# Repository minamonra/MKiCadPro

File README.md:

# MKiCadPro
MKiCadPro

Some of my projects

Use it - enjoy! :) ;)

minamonra@gmail.com

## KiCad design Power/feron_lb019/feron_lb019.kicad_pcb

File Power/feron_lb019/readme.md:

Блок питания 24 вольт, 150 Ватт, обратноход на ШИМ OB2269, частота при R18=27кОм - 65кГц.

Возможные варианты ШИМки CR6841/2, SG6841/2, SG5841/2, L2268/9, LD7551 (без Rt).

Размер корпуса 200x55.

[Обсудить можно тут.](https://anklab.ru/forum/index.php?topic=241.0)

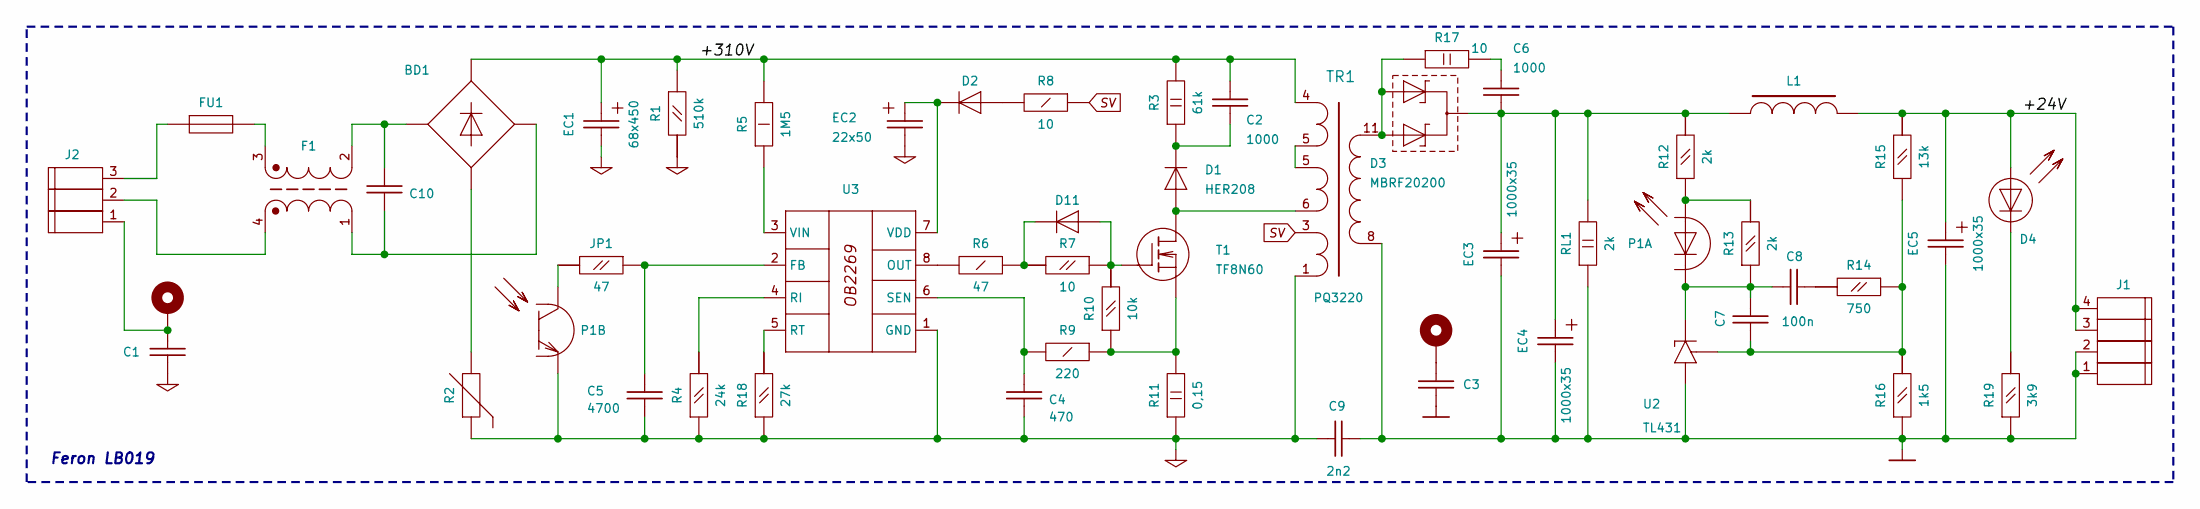
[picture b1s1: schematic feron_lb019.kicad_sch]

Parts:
BD1: BRIDGE; Diode_Bridge_19.0x3.5x10.0mm_P5.0mm
C1, C3: 1n; C_Disc_D5.0mm_W2.5mm_P5.00mm
C2, C6: 1000; C_Disc_D5.0mm_W2.5mm_P5.00mm
C4: 470; C_Disc_D5.0mm_W2.5mm_P5.00mm
C5: 4700; C_Disc_D5.0mm_W2.5mm_P5.00mm
C7: NA; C_Disc_D5.0mm_W2.5mm_P5.00mm
C8: 100n; C_Disc_D5.0mm_W2.5mm_P5.00mm
C9: 2n2; C_Disc_D5.0mm_W2.5mm_P5.00mm
C10: C_Rect_L9.0mm_W4.9mm_P7.50mm_MKT
D1: HER208; D_DO-15_P5.08mm_Vertical_KathodeUp
D2: DIODE; D_A-405_P10.16mm_Horizontal
D3: MBRF20200; TO-220-3-01
D4: LED; LED_D3.0mm
D11: DIODE; D_DO-34_SOD68_P10.16mm_Horizontal
EC1: 68x450; CP_L38.0mm_D18.0mm_P44.00mm_Horizontal
EC2: 22x50; CP_Radial_D6.3mm_P2.50mm
EC3, EC4, EC5: 1000x35; CP_Radial_D10.0mm_P5.00mm
F1: F; Filter-EMI-20x16_00
FU1: 1A; Fuse_Littelfuse_395Series
H2, H3: MountingHole_Pad; MountingHole_3.2mm_M3_DIN965_Pad
J1: Conn_4pin01; HB-8.25-4p
J2: Conn_3pin01; HB-8.25-3p
JP1: 47; R_Axial_DIN0207_L6.3mm_D2.5mm_P10.16mm_Horizontal
L1: LFERR; dross03
P1: PC817; DIP-4_W10.16mm_LongPads
R1: 510k; R_Axial_DIN0207_L6.3mm_D2.5mm_P10.16mm_Horizontal
R2: t°; RV_Disc_D12mm_W3.9mm_P7.5mm
R3: 61k; R_Axial_DIN0614_L14.3mm_D5.7mm_P5.08mm_Vertical
R4: 24k; R_Axial_DIN0207_L6.3mm_D2.5mm_P10.16mm_Horizontal
R5: 1M5; R_Axial_DIN0309_L9.0mm_D3.2mm_P15.24mm_Horizontal
R6: 47; R_Axial_DIN0207_L6.3mm_D2.5mm_P10.16mm_Horizontal
R7, R8: 10; R_Axial_DIN0207_L6.3mm_D2.5mm_P10.16mm_Horizontal
R9: 220; R_Axial_DIN0207_L6.3mm_D2.5mm_P10.16mm_Horizontal
R10: 10k; R_Axial_DIN0207_L6.3mm_D2.5mm_P10.16mm_Horizontal
R11: 0,15; R_Axial_DIN0516_L15.5mm_D5.0mm_P20.32mm_Horizontal
R12, R13: 2k; R_Axial_DIN0207_L6.3mm_D2.5mm_P10.16mm_Horizontal
R14: 750; R_Axial_DIN0207_L6.3mm_D2.5mm_P10.16mm_Horizontal
R15: 13k; R_Axial_DIN0207_L6.3mm_D2.5mm_P10.16mm_Horizontal
R16: 1k5; R_Axial_DIN0207_L6.3mm_D2.5mm_P10.16mm_Horizontal
R17: 10; R_Axial_DIN0516_L15.5mm_D5.0mm_P20.32mm_Horizontal
R18: 27k; R_Axial_DIN0207_L6.3mm_D2.5mm_P10.16mm_Horizontal
R19: 3k9; R_Axial_DIN0207_L6.3mm_D2.5mm_P10.16mm_Horizontal
RL1: 2k; R_Axial_DIN0516_L15.5mm_D5.0mm_P20.32mm_Horizontal
T1: TF8N60; TO-220-3-01
TR1: PQ3220; Transformer_PQ3220
U2: TL431; TO-92_IWm
U3: OB2268; DIP-8_W7.62mm

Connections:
/+24V: D4.2 (A), EC5.1, J1.3, J1.4, L1.2, R15.2
/+310V: BD1.1 (+), C2.2, EC1.1, R1.1, R3.2, R5.2, TR1.4
GND: C3.1, C9.1, EC3.2, EC4.2, EC5.2, J1.1, J1.2, R16.1, R19.1, RL1.1, TR1.7, TR1.8, TR1.9, U2.2 (A)
GND1: C1.1, C4.1, C5.1, C9.2, EC1.2, EC2.2, P1.3 (E), R1.2, R2.1, R4.1, R11.1, R18.1, TR1.1, U3.1 (GND)
unnamed: BD1.4 (-), R2.2
unnamed: BD1.2, C10.2, F1.2
unnamed: BD1.3, C10.1, F1.1
unnamed: C1.2, H2.1, J2.1
unnamed: C3.2, H3.1
unnamed: C6.2, R17.2
unnamed: C8.1, R14.2
unnamed: D1.2 (A), T1.2 (D), TR1.6
unnamed: C2.1, D1.1 (C), R3.1
unnamed: D2.2 (A), R8.2
unnamed: D2.1 (C), EC2.1, U3.7 (VDD)
unnamed: D3.1 (A1), D3.3 (A2), R17.1, TR1.10, TR1.11, TR1.12
unnamed: C6.1, D3.2 (K), EC3.1, EC4.1, L1.1, R12.2, RL1.2
unnamed: D4.1 (C), R19.2
unnamed: D11.2 (A), R7.1, R10.2, T1.1 (G)
unnamed: D11.1 (C), R6.1, R7.2
unnamed: F1.3, FU1.2
unnamed: F1.4, J2.2
unnamed: FU1.1, J2.3
unnamed: P1.1 (A), R12.1, R13.2
unnamed: C7.1, C8.2, P1.2 (C), R13.1, U2.3 (K)
unnamed: JP1.2, P1.4 (C)
unnamed: R9.1, R10.1, R11.2, T1.3 (S)
unnamed: C7.2, R14.1, R15.1, R16.2, U2.1 (REF)
unnamed: C5.2, JP1.1, U3.2 (FB)
unnamed: R6.2, U3.8 (OUT)
unnamed: R4.2, U3.4 (RI)
unnamed: R18.2, U3.5 (RT)
unnamed: C4.2, R9.2, U3.6 (SEN)
unnamed: R5.1, U3.3 (VIN)
SV: R8.1, TR1.3

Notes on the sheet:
Feron LB019

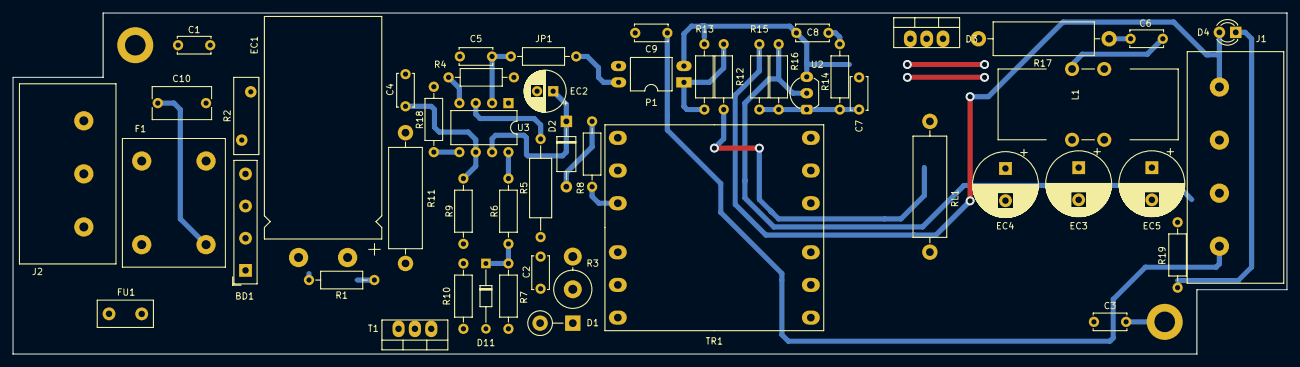
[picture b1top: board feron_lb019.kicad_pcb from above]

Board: 2 copper layers, 198.0 x 53.0 mm, 54 parts (0 on the bottom side), 35 nets.

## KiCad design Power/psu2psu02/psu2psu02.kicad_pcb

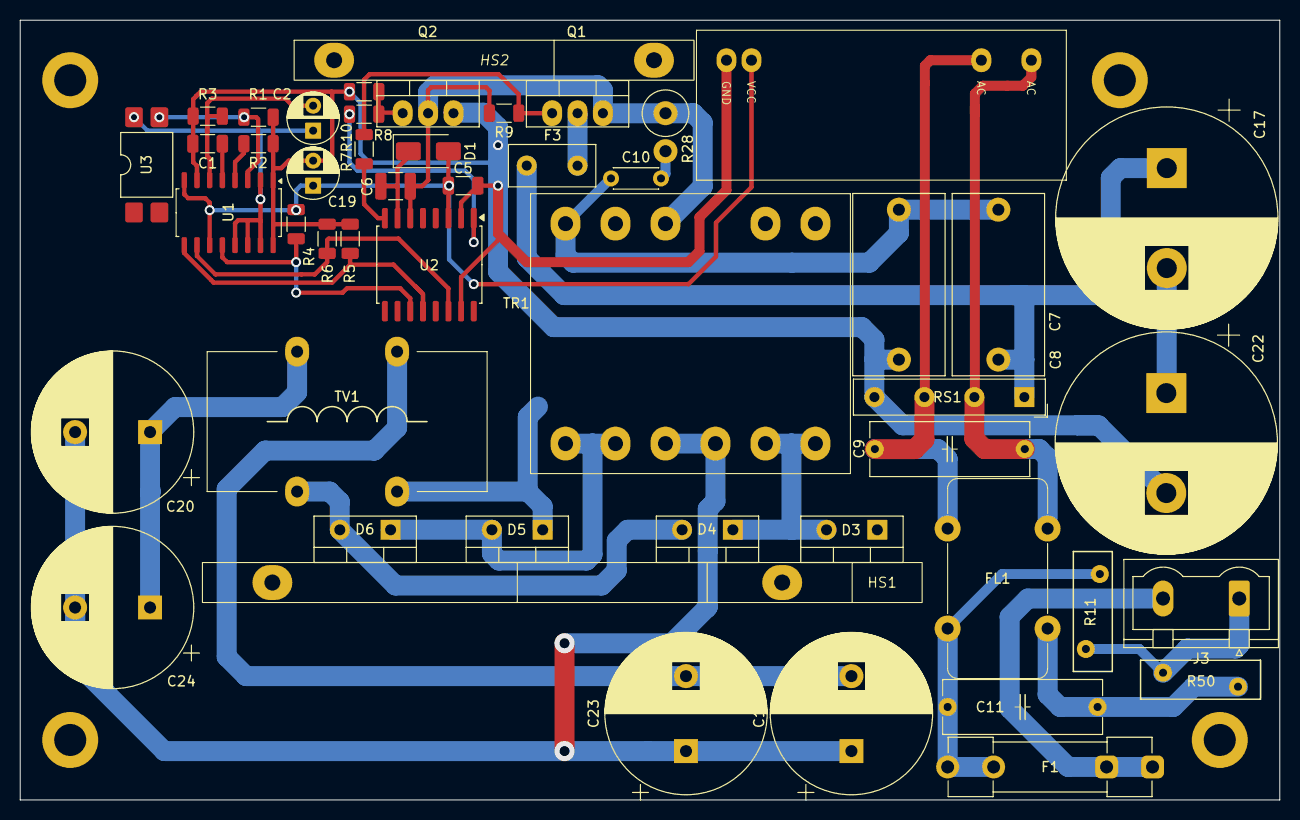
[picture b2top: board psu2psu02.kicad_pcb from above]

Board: 2 copper layers, 126.0 x 78.0 mm, 53 parts (0 on the bottom side), 34 nets.

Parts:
C1: 1000; C_1206_3216Metric
C2, C19: 10x35; CP_Radial_D5.0mm_P2.50mm
C5: 2,2; C_1206_3216Metric
C6: 2,2; C_1210_3225Metric
C7, C8: 1u; C_Rect_L18.0mm_W9.0mm_P15.00mm_FKS3_FKP3
C9, C11: 0,1; C_Rect_06-L16P15W5.8
C10: 4n7; C_Disc_D4.3mm_W1.9mm_P5.00mm
C17, C22: 330x200; CP_Radial_D22.0mm_P10.00mm_SnapIn
C18, C20, C23, C24: 1; CP_Radial_D16.0mm_P7.50mm
D1: ES1J; D_SMA
D3, D4, D5, D6: SF10A400H; TO-220-2_Vertical
F1: 1A; Fuseholder_Clip-5x20mm_Littelfuse_100_Inline_P20.50x4.60mm_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
F3: 3A; Fuse_Littelfuse_395Series
FL1: FEMI-FLEX01; EMIF02-FLEX
H1, H2, H3, H4: MountingHole; MountingHole_3.2mm_M3_DIN965_Pad
HS1: Heatsink_Pad; HeatsinkFLEX-200A-1
HS2: Heatsink_Pad; HeatsinkFLEX-200A-2
J3: Conn_2pin01; PhoenixContact_GMSTBVA_2,5_2-G-7,62_1x02_P7.62mm_Vertical
J6: ACDC_China-01; ACDC_China-04
Q1, Q2: 740; TO-220-3-01
R1, R9, R10: 1k; R_1206_3216Metric
R2, R5, R6: 10k; R_1206_3216Metric
R3: 11k; R_1206_3216Metric
R4: 27; R_1206_3216Metric
R7, R8: 33; R_1206_3216Metric
R11: 07K180; RV_Disc_D12mm_W3.9mm_P7.5mm
R28: 3k; RES2WV01
R50: t°; RV_Disc_D12mm_W3.9mm_P7.5mm
RS1: BRIDGE; Diode_Bridge_19.0x3.5x10.0mm_P5.0mm
TR1: HB-FLEX-200A-1; E36-FLEX-200A-P
TV1: TV; DRO05-FLEX-200A
U1: TL494IDR; SOIC-16_4.55x10.3mm_P1.27mm
U2: IR2113S; SOIC-16W_7.5x10.3mm_P1.27mm
U3: PC817; SMDIP-4_W9.53mm

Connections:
+HV: C7.2, C17.1, F3.2, RS1.1 (+)
/HV4: C6.1, Q1.3 (S), Q2.2 (D), R9.2, R28.1, TR1.4, U2.6 (Vs)
/HV6: C7.1, C8.2, C10.1, TR1.6
GND: C18.1, C20.2, C23.1, C24.2, TR1.9, TR1.10
GND2: C1.2, C5.1, C8.1, C19.2, C22.2, J6.4 (GND), Q2.3 (S), R1.1, R2.1, R3.1, R5.2, R6.2, R10.2, RS1.4 (-), U1.1 (1IN+), U1.7 (GND), U1.16 (2IN+), U2.2 (COM), U2.15 (Vss)
unnamed: C9.1, FL1.1, J6.2 (AC), RS1.3
unnamed: C9.2, FL1.2, J6.1 (AC), RS1.2
unnamed: C10.2, R28.2
unnamed: C11.1, F1.2, FL1.3, R11.1
unnamed: C11.2, FL1.4, R50.2
unnamed: C17.2, C22.1
unnamed: C18.2, C23.2, TV1.3
unnamed: C20.1, C24.1, TV1.4
unnamed: C6.2, D1.1 (C), U2.7 (Vb)
unnamed: D3.2 (A), D4.1 (C), TR1.11, TR1.12
unnamed: D3.1 (C), D5.1 (C), TV1.1
unnamed: D4.2 (A), D6.2 (A), TV1.2
unnamed: D5.2 (A), D6.1 (C), TR1.7, TR1.8
unnamed: F1.1, J3.2
unnamed: J3.1, R11.2, R50.1
unnamed: F3.1, Q1.2 (D)
unnamed: Q1.1 (G), R7.2, R9.1
unnamed: Q2.1 (G), R8.2, R10.1
unnamed: C2.1, U1.2 (1IN-), U1.13 (OTC), U1.14 (REF), U1.15 (2IN-), U3.4 (C)
unnamed: C1.1, U1.5 (CT)
unnamed: R2.2, U1.4 (DTC)
unnamed: R5.1, U1.9 (E1), U2.12 (Hin)
unnamed: R6.1, U1.10 (E2), U2.14 (Lin)
unnamed: R1.2, U1.3 (FB), U3.3 (E)
unnamed: C2.2, R3.2, U1.6 (RT)
unnamed: R4.1, U1.12 (VCC), U2.11 (Vdd)
unnamed: R7.1, U2.8 (HO)
unnamed: R8.1, U2.1 (LO)
VCC: C5.2, C19.1, D1.2 (A), J6.3 (VCC), R4.2, U1.8 (C1), U1.11 (C2), U2.3 (Vcc)

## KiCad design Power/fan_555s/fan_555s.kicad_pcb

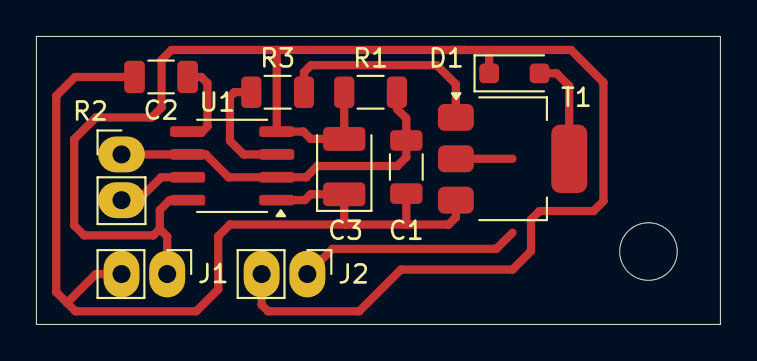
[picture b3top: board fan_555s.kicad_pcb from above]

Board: 2 copper layers, 38.0 x 16.0 mm, 12 parts (0 on the bottom side), 8 nets.

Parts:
C1, C2: 0,1; C_1206_3216Metric
C3: 10,0; CP_EIA-3528-21_Kemet-B
D1: 4148; D_SOD-123F
H1: MountingHole; MountingHole_3.2mm_M3
J1, J2: Conn_2pin01; PinHeader_1x02_P2.54mm_Vertical
R1: 22k; R_1206_3216Metric
R2: 10k/NTC; PinHeader_1x02_P2.54mm_Vertical
R3: 100; R_1206_3216Metric
T1: 1N60G; SOT-223-3_TabPin2
U1: NE555; SOIC-8_3.9x4.9mm_P1.27mm

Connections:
GND: C1.1, C2.1, C3.1, J1.2, T1.3 (S), U1.1 (GND)
unnamed: D1.2 (A), J2.1, T1.2 (D)
unnamed: C3.2, D1.1 (C), J1.1, J2.2, R1.2, U1.4 (RST), U1.8 (VCC)
unnamed: R3.2, T1.1 (G)
unnamed: C2.2, U1.5 (CTL)
unnamed: R2.2, U1.7 (DIS)
unnamed: R3.1, U1.3 (OUT)
unnamed: C1.2, R1.1, R2.1, U1.2 (TRG), U1.6 (THR)

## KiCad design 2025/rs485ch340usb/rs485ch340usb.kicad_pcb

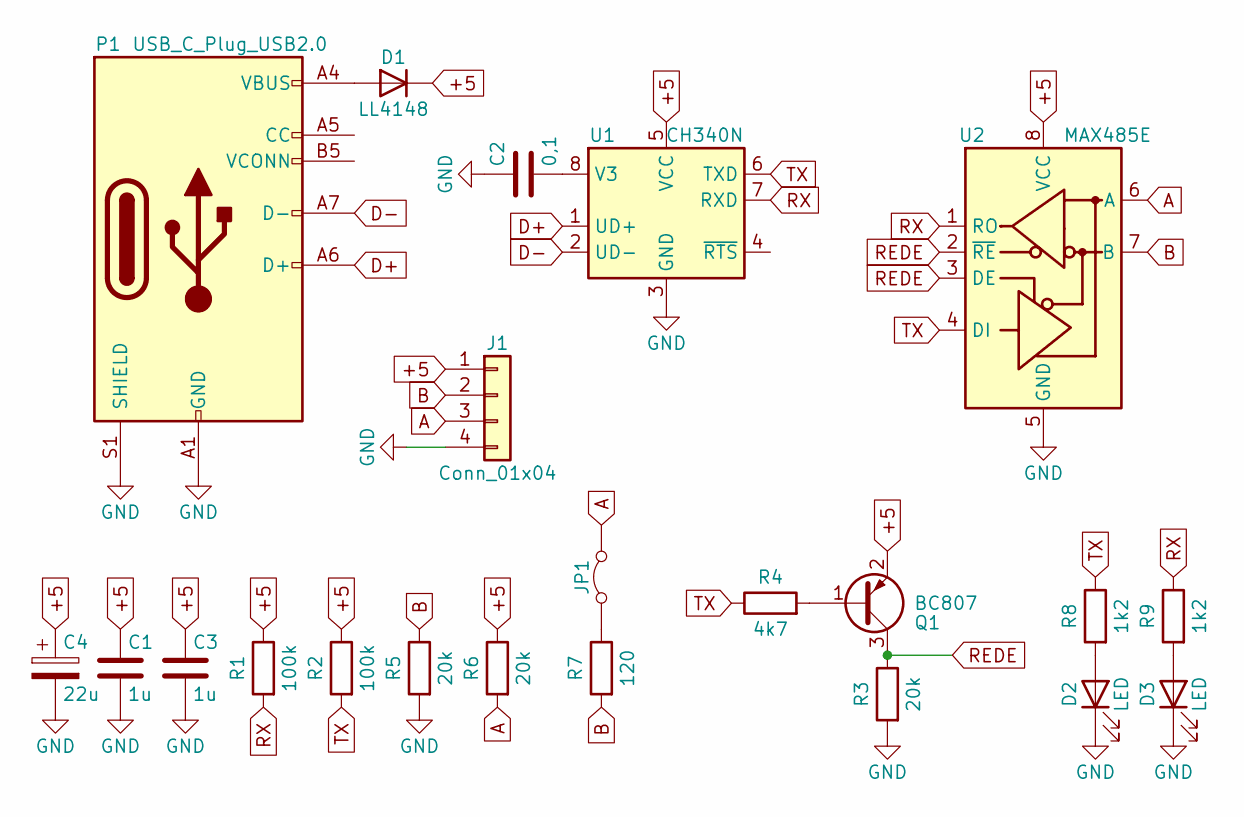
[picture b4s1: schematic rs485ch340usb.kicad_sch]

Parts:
C1, C3: 1u; C_1206_3216Metric
C2: 0,1; C_1206_3216Metric
C4: 22u; CP_EIA-3528-21_Kemet-B
D1: LL4148; D_MiniMELF
D2, D3: LED; LED_1206_3216Metric
J1: Conn_01x04; TerminalBlock_bornier-4_P5.08mm
JP1: Jumper_2_Bridged; PinHeader_1x02_P2.54mm_Vertical
P1: USB_C_Plug_USB2.0; USB_C_Plug_JAE_DX07P024AJ1
Q1: BC807; SOT-23
R1, R2: 100k; R_1206_3216Metric
R3, R5, R6: 20k; R_1206_3216Metric
R4: 4k7; R_1206_3216Metric
R7: 120; R_1206_3216Metric
R8, R9: 1k2; R_1206_3216Metric
U1: CH340N; SOP-8_3.9x4.9mm_P1.27mm
U2: MAX485E; SOIC-8_3.9x4.9mm_P1.27mm

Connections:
+5: C1.1, C3.1, C4.1, D1.1 (K), J1.1, Q1.2 (E), R1.1, R2.1, R6.1, U1.5 (VCC), U2.8 (VCC)
A: J1.3, JP1.2 (B), R6.2, U2.6 (A)
B: J1.2, R5.1, R7.2, U2.7 (B)
D+: P1.A6 (D+), U1.1 (UD+)
D-: P1.A7 (D-), U1.2 (UD-)
GND: C1.2, C2.1, C3.2, C4.2, D2.1 (K), D3.1 (K), J1.4, P1.A1 (GND), P1.A12 (GND), P1.B1 (GND), P1.B12 (GND), P1.S1 (SHIELD), R3.2, R5.2, U1.3 (GND), U2.5 (GND)
unnamed: D1.2 (A), P1.A4 (VBUS), P1.A9 (VBUS), P1.B4 (VBUS), P1.B9 (VBUS)
unnamed: D2.2 (A), R8.2
unnamed: D3.2 (A), R9.2
unnamed: JP1.1 (A), R7.1
unnamed: Q1.1 (B), R4.2
unnamed: C2.2, U1.8 (V3)
REDE: Q1.3 (C), R3.1, U2.2 (~RE), U2.3 (DE)
RX: R1.2, R9.1, U1.7 (RXD), U2.1 (RO)
TX: R2.2, R4.1, R8.1, U1.6 (TXD), U2.4 (DI)

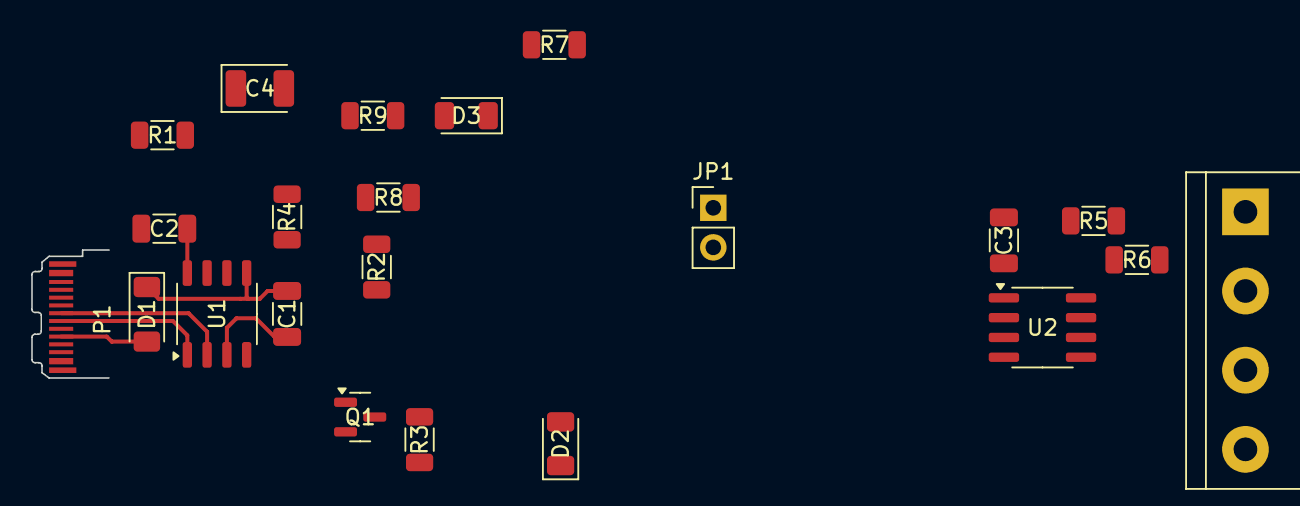
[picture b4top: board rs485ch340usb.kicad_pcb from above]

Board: 2 copper layers, 22 parts (0 on the bottom side), 15 nets.

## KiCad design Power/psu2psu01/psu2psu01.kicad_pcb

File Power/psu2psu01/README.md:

For details see:
https://anklab.ru/forum/index.php?topic=197

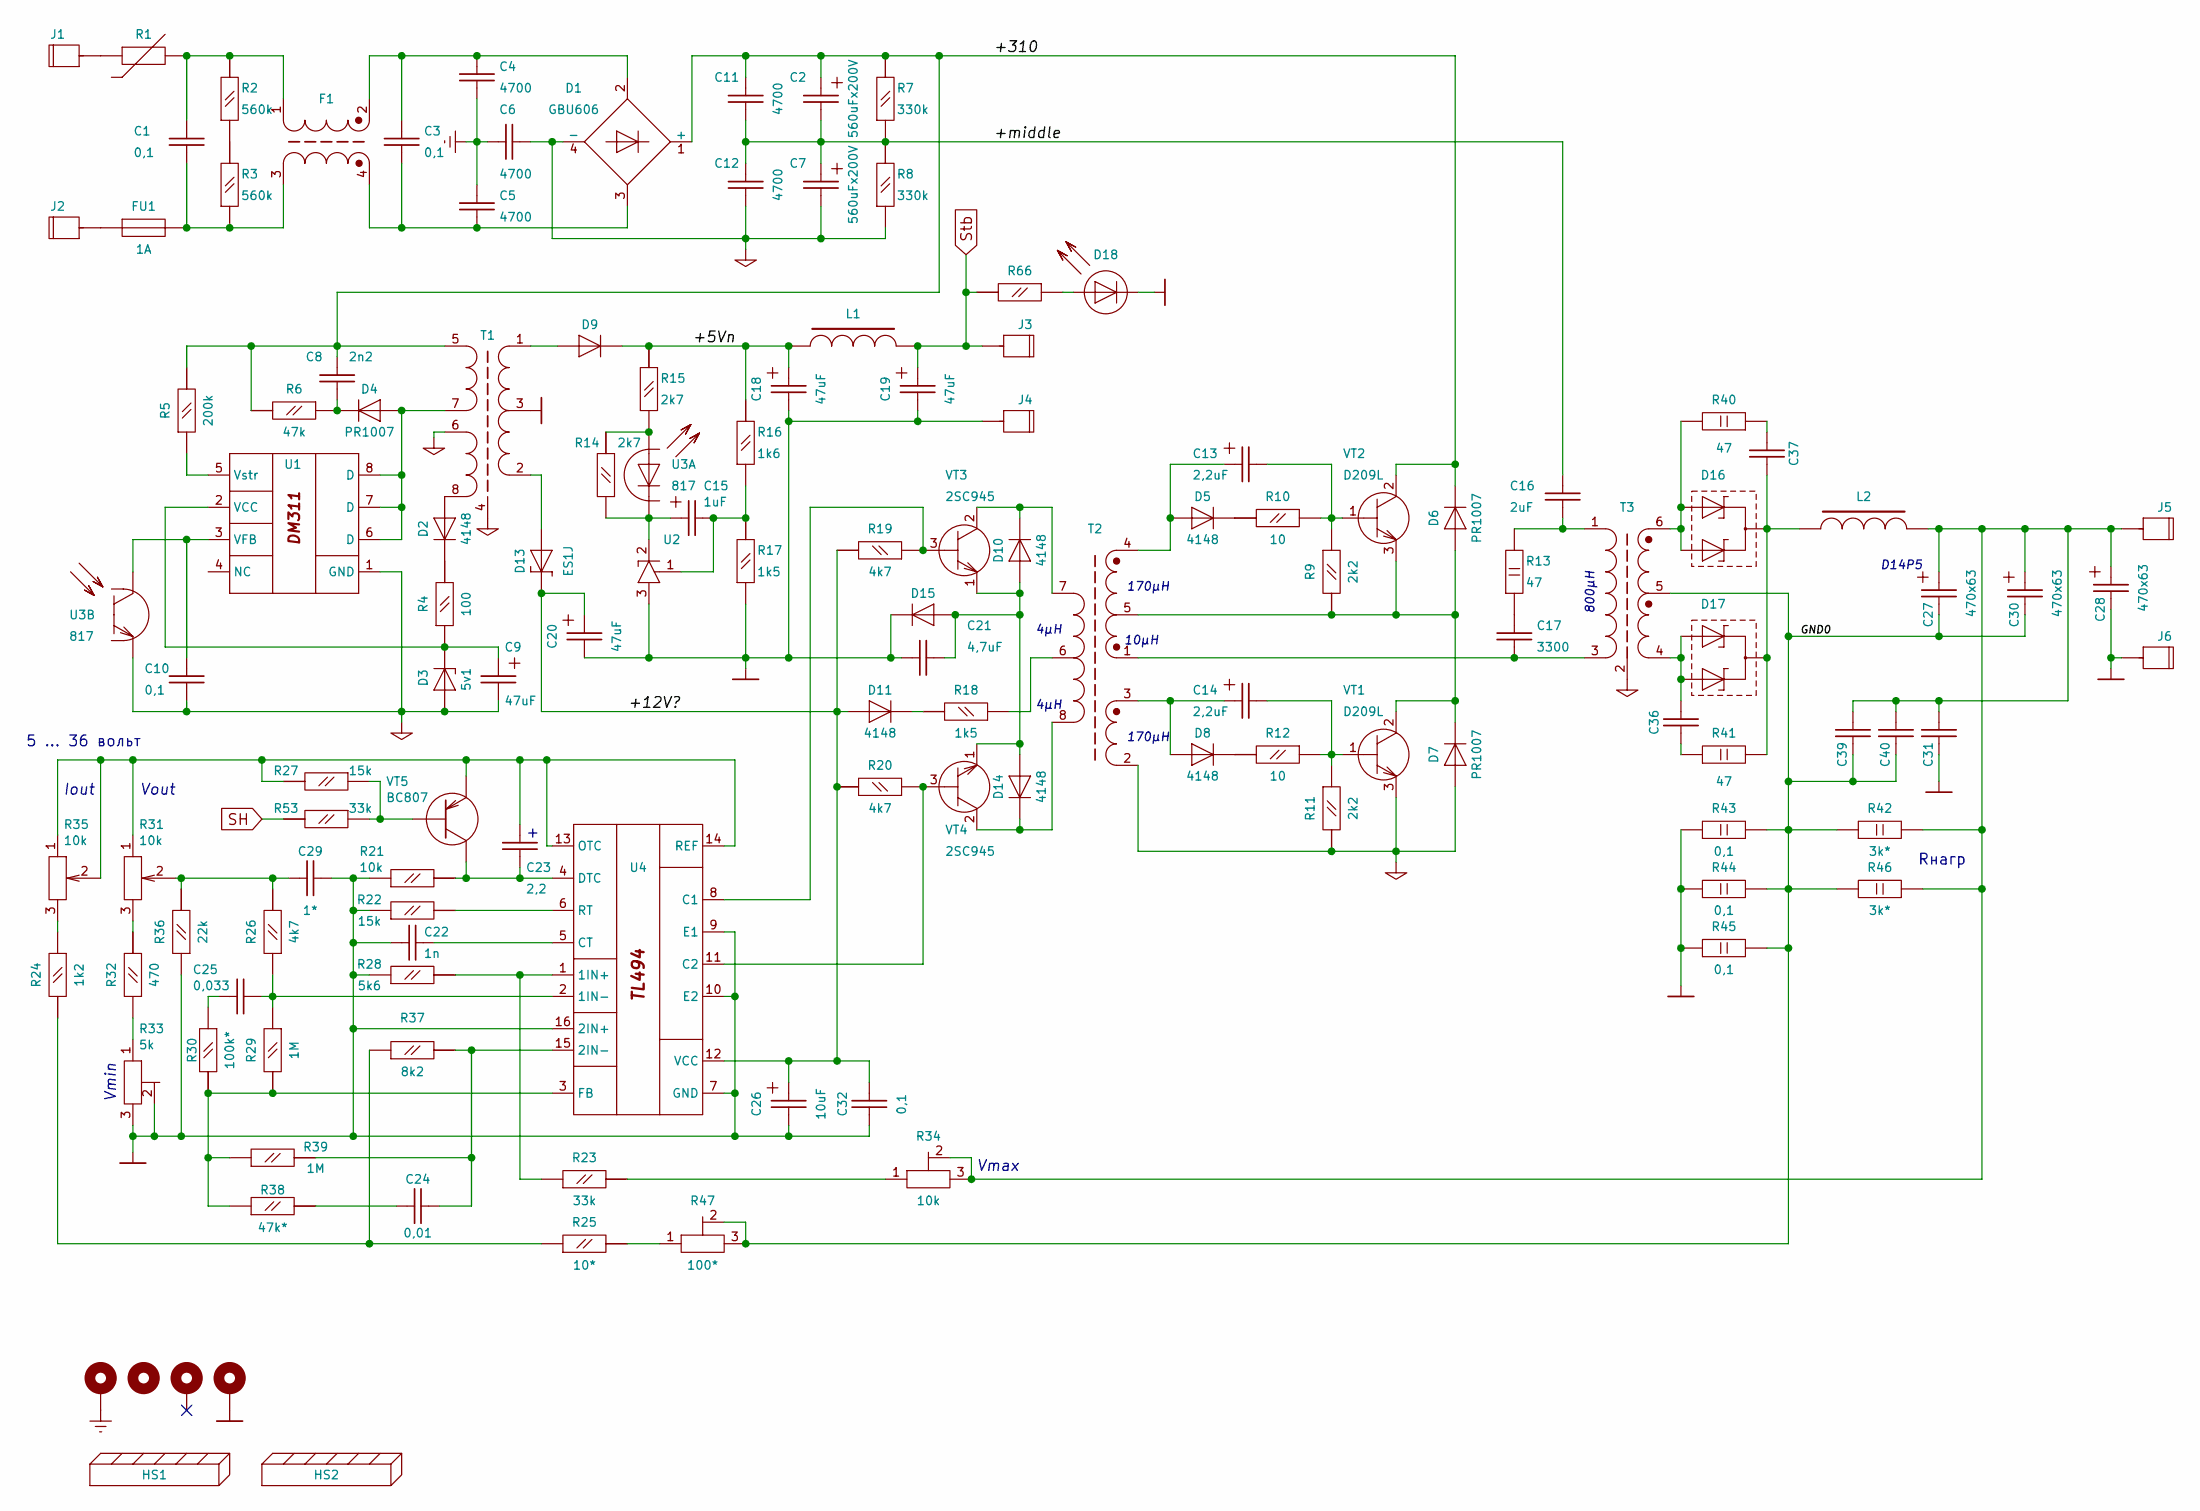
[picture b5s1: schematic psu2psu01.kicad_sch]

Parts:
C1: 0,1; C_Rect_L16.5mm_W10.9mm_P15.00mm_MKT
C2, C7: 560uFx200V; CP3
C3: 0,1; C_Rect_L16.5mm_W6.0mm_P15.00mm_MKT
C4, C5, C6: 4700; CPD11mmW5mmP10mm01
C8: 2n2; C_Disc_D3.0mm_W2.0mm_P2.50mm
C9: 47uF; CP_Radial_D5.0mm_P2.50mm
C10, C36, C37: 0,1; C_Disc_D3.0mm_W2.0mm_P2.50mm
C11, C12: 4700; CPD01
C13, C14: 2,2uF; CP_Radial_D5.0mm_P2.50mm
C15: 1uF; C_1206_3216Metric
C16: 2uF; CP2
C17: 3300; C_Disc_D7.5mm_W2.5mm_P5.00mm
C18, C19, C20: 47uF; CP_Radial_D6.3mm_P2.50mm
C21: 4,7uF; C_1206_3216Metric
C22: 1n; C_1206_3216Metric
C23: 2,2; C_1206_3216Metric
C24: 0,01; C_1206_3216Metric
C25: 0,033; C_1206_3216Metric
C26: 10uF; CP_Radial_D6.3mm_P2.50mm
C27, C30: 470x63; CP_Radial_D14.0mm_P5.00mm
C28: 470x63; CP4
C29: 1*; C_1206_3216Metric
C31, C32, C39, C40: 0,1; C_1206_3216Metric
D1: GBU606; Diode_Bridge_Vishay_GBU
D2, D5, D8, D10, D11, D14: 4148; D_1206_3216Metric
D3: 5v1; D_1206_3216Metric
D4: PR1007; Diode10mm-DA-405
D6, D7, D15: PR1007; D_A-405_P7.62mm_Horizontal
D9: D_DO-15_P5.08mm_Vertical_AnodeUp
D13: ES1J; D_SMA
D16, D17: TO-220-3-01
D18: LED; LED_1206_3216Metric_ReverseMount_Hole1.8x2.4mm
F1: F; EMIF
FU1: 1A; Fuse_Bourns_MF-RG500
H1, H2, H3: Earth; MountingHole_3.2mm_M3_Pad
H4: MountingHole; MountingHole_3.2mm_M3
HS1: RADIATOR2PSU1; Radiator_2PSU1
HS2: RADIATOR2PSU1; Radiator_2PSU2
J1, J2, J5, J6: CONN01PIN; 1PIN2mmD
J3, J4: CONN01PIN; 1PIN1.4mmD
L1: LFERR; dross01
L2: LFERR; dross02
R1: t°; CPD1
R2, R3: 560k; R_1206_3216Metric
R4: 100; R_1206_3216Metric
R5: 200k; R_Axial_DIN0207_L6.3mm_D2.5mm_P10.16mm_Horizontal
R6: 47k; R_Axial_DIN0207_L6.3mm_D2.5mm_P10.16mm_Horizontal
R7, R8: 330k; C_1206_3216Metric
R9, R11: 2k2; R_Axial_DIN0207_L6.3mm_D2.5mm_P10.16mm_Horizontal
R10, R12, R66: 10; R_1206_3216Metric
R13: 47; R_Axial_DIN0414_L11.9mm_D4.5mm_P7.62mm_Vertical
R14, R15: 2k7; C_1206_3216Metric
R16: 1k6; C_1206_3216Metric
R17, R18: 1k5; C_1206_3216Metric
R19, R20, R26: 4k7; C_1206_3216Metric
R21: 10k; C_1206_3216Metric
R22, R27: 15k; C_1206_3216Metric
R23, R53: 33k; C_1206_3216Metric
R24: 1k2; C_1206_3216Metric
R25: 10*; C_1206_3216Metric
R28: 5k6; C_1206_3216Metric
R29, R39: 1M; C_1206_3216Metric
R30: 100k*; C_1206_3216Metric
R31, R35: 10k; PinHeader_1x03_P2.54mm_Vertical
R32: 470; C_1206_3216Metric
R33: 5k; Potentiometer_Bourns_3296W_Vertical
R34: 10k; Potentiometer_Bourns_3296W_Vertical
R36: 22k; C_1206_3216Metric
R37: 8k2; C_1206_3216Metric
R38: 47k*; C_1206_3216Metric
R40, R41: 47; RES2WV01
R42, R46: 3k*; RES2WV01
R43, R44, R45: 0,1; R_2512_6332Metric
R47: 100*; Potentiometer_Bourns_3296W_Vertical
T1: HM1243; Transformer_HM1243
T2: YC13006; Transformer_YC1306
T3: HB13006; Transformer_HB1306
U1: DM311; DIP-8_W7.62mm
U2: TL431LP; SOT-23
U3: 817; DIP-4_W10.16mm
U4: TL494IDR; SOIC-16_4.55x10.3mm_P1.27mm
VT1, VT2: D209L; TO-3PB-3_Vertical
VT3, VT4: 2SC945; TO-92IW
VT5: BC807; SOT-23

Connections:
/+5Vn: C18.1, D9.1 (C), L1.1, R15.2, R16.2
/+12V?: C20.1, C26.1, C32.2, D11.2 (A), D13.1 (C), R19.2, R20.2, U4.12 (VCC)
/+310: C2.1, C8.2, C11.2, D1.1 (+), D6.1 (C), R5.2, R6.2, R7.2, T1.5, VT2.2 (C)
/+middle: C2.2, C7.1, C11.1, C12.2, C16.2, R7.1, R8.2
/GND0: C27.2, C30.2, C39.2, C40.2, HS2.1, R42.1, R43.2, R44.2, R45.2, R46.2, R47.2, R47.3, T3.5
Earth: C4.1, C5.2, C6.2, H1.1
GND: C18.2, C19.2, C20.2, C21.2, C22.1, C26.2, C28.2, C29.1, C31.2, C32.1, D15.1 (C), D18.1 (C), H3.1, J4.1, J6.1, R17.1, R21.1, R22.1, R28.1, R33.2, R33.3, R36.1, R43.1, R44.1, R45.1, T1.3, U2.3 (A), U4.7 (GND), U4.9 (E1), U4.10 (E2), U4.16 (2IN+)
GND1: C6.1, C7.2, C9.2, C10.1, C12.1, D1.4 (-), D3.2 (A), D7.2 (A), R8.1, R11.2, T1.4, T1.6, T2.2, T3.2, U1.1 (GND), U3.3 (E), VT1.3 (E)
unnamed: C1.1, F1.3, FU1.2, R3.1
unnamed: C1.2, F1.1, R1.2, R2.2
unnamed: C3.1, C5.1, D1.3, F1.4
unnamed: C3.2, C4.2, D1.2, F1.2
unnamed: C16.1, R13.2, T3.1
unnamed: C17.1, T2.1, T3.3
unnamed: C17.2, R13.1
unnamed: C24.1, R38.2
unnamed: C25.1, R30.1
unnamed: C27.1, C28.1, C30.1, C31.1, C39.1, C40.1, J5.1, L2.2, R34.2, R34.3, R42.2, R46.1
unnamed: C29.2, R26.2, R31.2, R36.2
unnamed: C36.2, R41.1
unnamed: C37.1, R40.1
unnamed: D2.2 (A), T1.8
unnamed: D2.1 (C), R4.2
unnamed: C9.1, D3.1 (C), R4.1, U1.2 (VCC)
unnamed: D4.2 (A), T1.7, U1.6 (D), U1.7 (D), U1.8 (D)
unnamed: C8.1, D4.1 (C), R6.1
unnamed: C13.1, D5.2 (A), T2.4
unnamed: D5.1 (C), R10.2
unnamed: D6.2 (A), D7.1 (C), R9.2, T2.5, VT1.2 (C), VT2.3 (E)
unnamed: C14.1, D8.2 (A), T2.3
unnamed: D8.1 (C), R12.2
unnamed: D9.2 (A), T1.1
unnamed: C21.1, D10.2 (A), D14.2 (A), D15.2 (A), VT3.1 (E), VT4.1 (E)
unnamed: D10.1 (C), T2.7, VT3.2 (C)
unnamed: D11.1 (C), R18.2
unnamed: D13.2 (A), T1.2
unnamed: D14.1 (C), T2.8, VT4.2 (C)
unnamed: D16.1 (A1), D16.3 (A2), R40.2, T3.6
unnamed: C37.2, D16.2 (K), D17.2 (K), L2.1, R41.2
unnamed: C36.1, D17.1 (A1), D17.3 (A2), T3.4
unnamed: D18.2 (A), R66.1
unnamed: FU1.1, J2.1
unnamed: J1.1, R1.1
unnamed: R2.1, R3.2
unnamed: R18.1, T2.6
unnamed: R23.2, R34.1
unnamed: R24.1, R35.3
unnamed: R24.2, R25.1, R37.1
unnamed: R25.2, R47.1
unnamed: R31.3, R32.2
unnamed: R32.1, R33.1
unnamed: C10.2, U1.3 (VFB), U3.4 (C)
unnamed: R5.1, U1.5 (Vstr)
unnamed: C15.1, R14.1, U2.2 (K), U3.2 (C)
unnamed: C15.2, R16.1, R17.2, U2.1 (REF)
unnamed: R14.2, R15.1, U3.1 (A)
unnamed: R23.1, R28.2, U4.1 (1IN+)
unnamed: C25.2, R26.1, R29.1, U4.2 (1IN-)
unnamed: C24.2, R37.2, R39.2, U4.15 (2IN-)
unnamed: R19.1, U4.8 (C1), VT3.3 (B)
unnamed: R20.1, U4.11 (C2), VT4.3 (B)
unnamed: C22.2, U4.5 (CT)
unnamed: C23.1, R21.2, U4.4 (DTC), VT5.3 (C)
unnamed: R29.2, R30.2, R38.1, R39.1, U4.3 (FB)
unnamed: C23.2, R27.2, R31.1, R35.1, R35.2, U4.13 (OTC), U4.14 (REF), VT5.2 (E)
unnamed: R22.2, U4.6 (RT)
unnamed: C14.2, R11.1, R12.1, VT1.1 (B)
unnamed: C13.2, R9.1, R10.1, VT2.1 (B)
unnamed: R27.1, R53.1, VT5.1 (B)
SH: R53.2
Stb: C19.1, J3.1, L1.2, R66.2

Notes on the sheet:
4μH
Iout
Vmax
Vout
Rнагр
D14P5
170μH
10μH
Vmin
5 ... 36 вольт
800μH

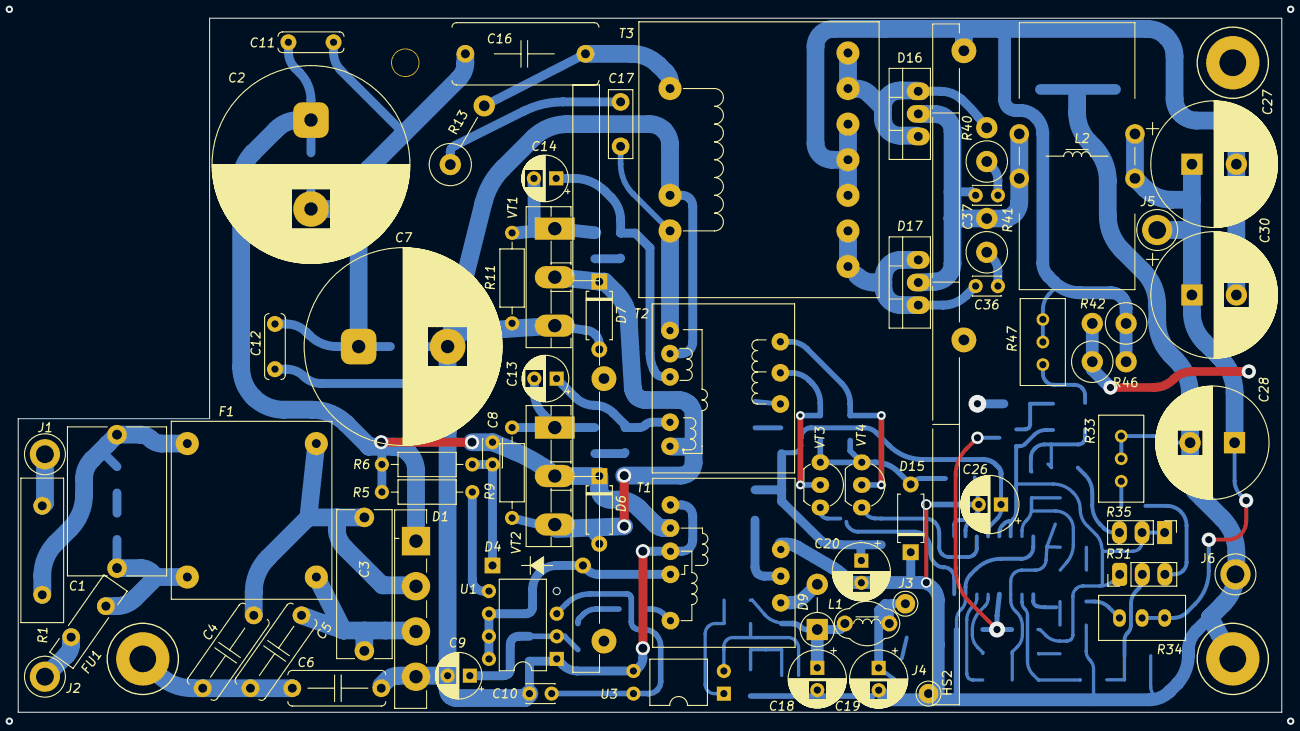
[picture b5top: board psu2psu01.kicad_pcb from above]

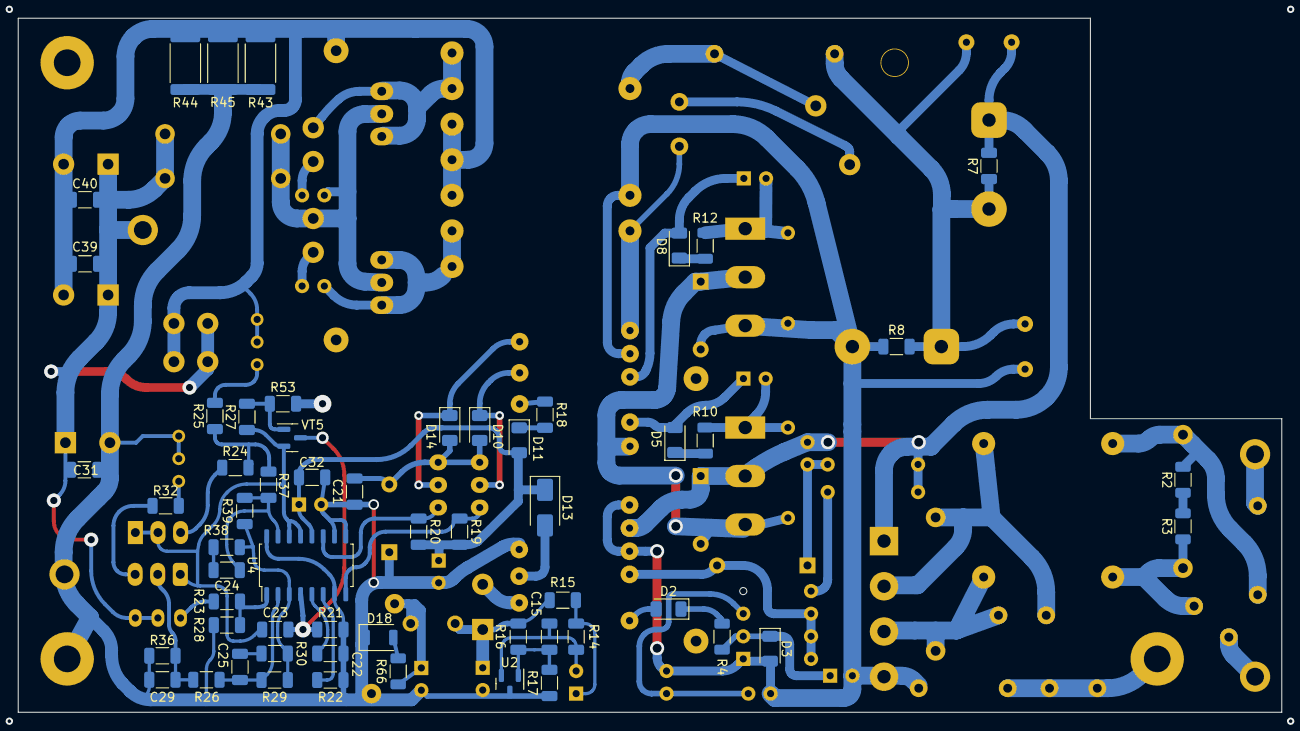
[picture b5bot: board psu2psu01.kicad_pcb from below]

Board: 2 copper layers, 142.0 x 78.0 mm, 130 parts (57 on the bottom side), 70 nets.

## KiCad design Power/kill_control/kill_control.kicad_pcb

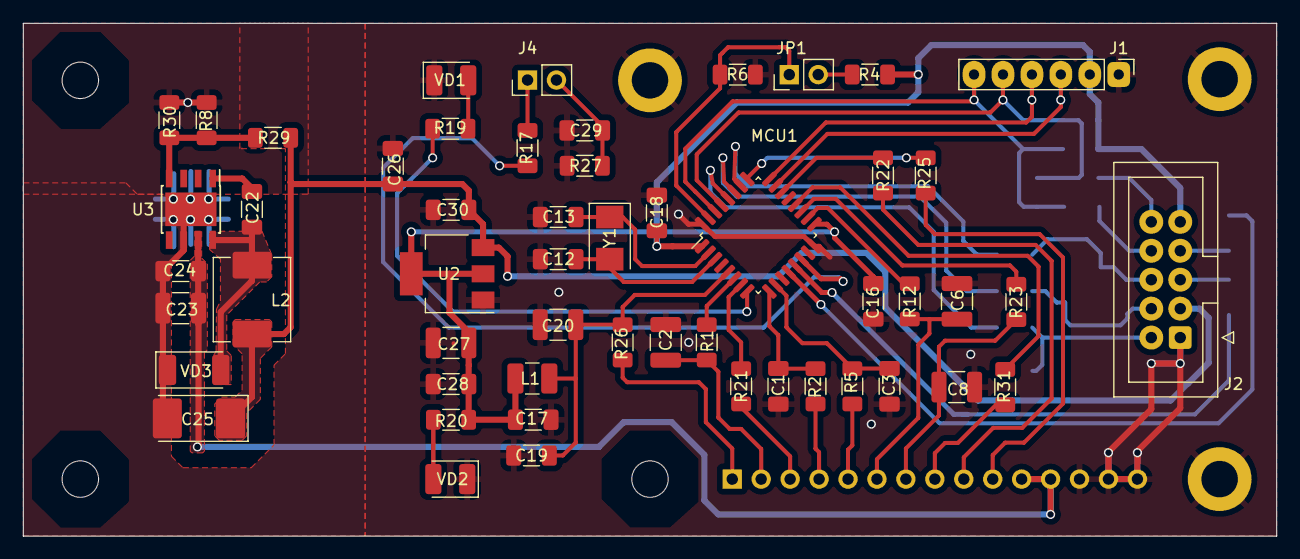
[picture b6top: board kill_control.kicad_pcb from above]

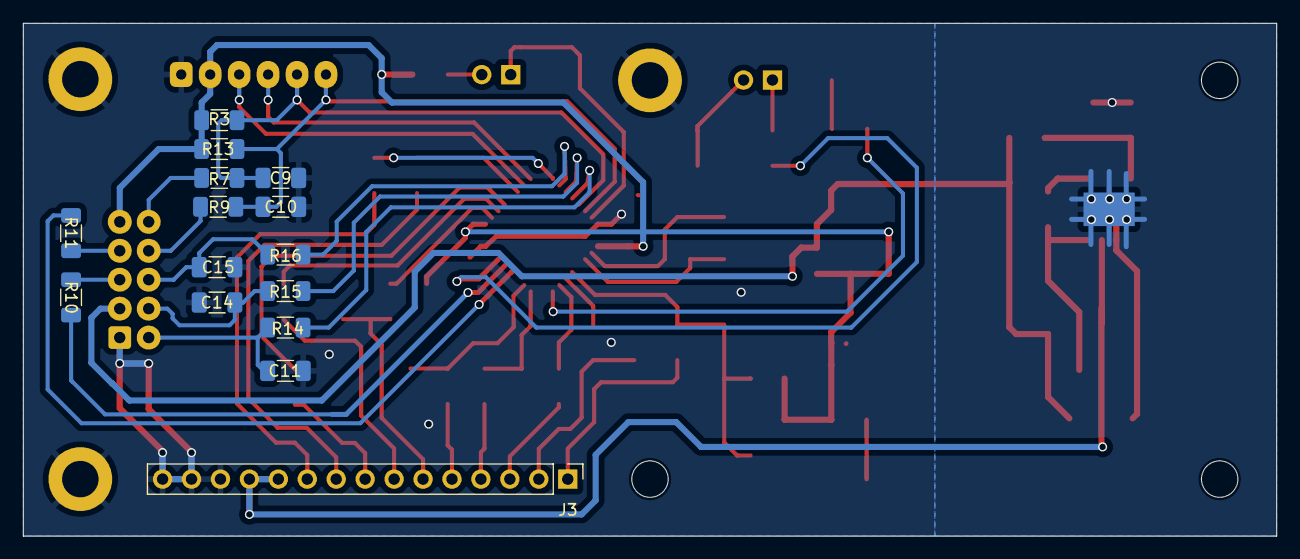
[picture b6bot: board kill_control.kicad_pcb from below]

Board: 2 copper layers, 110.0 x 45.0 mm, 74 parts (15 on the bottom side), 53 nets.

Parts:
C1, C3, C22: 0,01; C_1206_3216Metric_Pad1.33x1.80mm_HandSolder
C2: 0,01; C_1210_3225Metric_Pad1.33x2.70mm_HandSolder
C6, C8: 4,7; C_1210_3225Metric_Pad1.33x2.70mm_HandSolder
C9, C10: 100*; C_1206_3216Metric_Pad1.33x1.80mm_HandSolder
C11, C14, C15: 100; C_1206_3216Metric_Pad1.33x1.80mm_HandSolder
C12, C13: 15; C_1206_3216Metric_Pad1.33x1.80mm_HandSolder
C16, C17, C18, C19, C24, C26, C28, C29, C30: 0,1; C_1206_3216Metric_Pad1.33x1.80mm_HandSolder
C20, C23: 22,0; C_1210_3225Metric_Pad1.33x2.70mm_HandSolder
C25: 220,0; CP_EIA-7132-20_AVX-U
C27: 47,0; C_1210_3225Metric_Pad1.33x2.70mm_HandSolder
H1, H2, H3: MountingHole; MountingHole_3.2mm_M3
H4, H5, H6: MountingHole_Pad; MountingHole_3.2mm_M3_DIN965_Pad
J1: Debug; PinHeader_1x06_P2.54mm_Vertical_zm
J2: IDC-Header_2x05_P2.54_V01
J3: PinHeader_1x15_P2.54mm_Vertical
J4: t; PinHeader_1x02_P2.54mm_Vertical
JP1: Boot; PinHeader_1x02_P2.54mm_Vertical
L1: 100мкГн; L_1210_3225Metric_Pad1.42x2.65mm_HandSolder
L2: 22мкГн; L_Abracon_ASPI-0630LR
MCU1: STM32F030K6Tx; LQFP-32_7x7mm_P0.8mm
R1: 2k7; R_1206_3216Metric_Pad1.30x1.75mm_HandSolder
R2, R4, R5, R12: 1k; R_1206_3216Metric_Pad1.30x1.75mm_HandSolder
R3, R13: 15k; R_1206_3216Metric_Pad1.30x1.75mm_HandSolder
R6, R27, R29: 10k; R_1206_3216Metric_Pad1.30x1.75mm_HandSolder
R7, R9, R10, R11, R14, R15, R16: 22; R_1206_3216Metric_Pad1.30x1.75mm_HandSolder
R8: *; R_1206_3216Metric_Pad1.30x1.75mm_HandSolder
R17, R31: 10; R_1206_3216Metric_Pad1.30x1.75mm_HandSolder
R19, R20: 2k; R_1206_3216Metric_Pad1.30x1.75mm_HandSolder
R21, R22, R25, R26: 150; R_1206_3216Metric_Pad1.30x1.75mm_HandSolder
R23: 3k; R_1206_3216Metric_Pad1.30x1.75mm_HandSolder
R30: 3,24k; R_1206_3216Metric_Pad1.30x1.75mm_HandSolder
U2: AMS1117-3.3; SOT-223-3_TabPin2
U3: TPS5430DDA; TI_SO-PowerPAD-8_ThermalViasV1
VD1, VD2: LED_1210_3225Metric_Pad1.42x2.65mm_HandSolder
VD3: D_2010_5025Metric_Pad1.52x2.65mm_HandSolder
Y1: 12MHz*; Crystal_SMD_5032-2Pin_5.0x3.2mm

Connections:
+5V: C25.1, C26.1, C30.1, J2.3, L2.2, R29.2, U2.3 (VI)
+15V: C23.1, C24.1, J3.11, J3.12, U3.7 (VIN)
/ADC_IN3: C1.1, MCU1.9 (PA3), R2.1
/ADC_IN4: C3.1, MCU1.10 (PA4), R5.1
/PH: C22.2, L2.1, U3.8 (PH), VD3.2 (C)
/TIM1_CH1: MCU1.18 (PA8), R12.2
/TIM1_CH2: MCU1.19 (PA9), R23.2
ADC_IN8: MCU1.14 (PB0), R17.2
AUDIO: C2.2, J3.2, R1.1
BOOT: JP1.1 (A), MCU1.31 (Boot), R6.1
ENCA: MCU1.13 (PA7), R10.1
ENCB: MCU1.12 (PA6), R11.1
FANch: J3.8, R31.1
GND: C1.2, C2.1, C3.2, C6.2, C8.2, C9.2, C10.2, C11.2, C12.2, C13.2, C14.2, C15.2, C16.2, C17.2, C18.2, C19.2, C20.2, C23.2, C24.2, C25.2, C26.2, C27.2, C28.2, C29.2, C30.2, H4.1, H5.1, H6.1, J1.1, J3.13, J3.14, J3.15, MCU1.16 (Gnd), MCU1.32 (Gnd), R6.2, R8.2, R27.2, R30.2, U2.1 (GND), U3.6 (GND), U3.9 (GNDPAD), VD1.1 (K), VD2.1 (K), VD3.1 (A)
IFB: J3.4, R2.2
LED1: MCU1.8 (PA2), R19.1
unnamed: C11.1, J2.2, R14.2
unnamed: C14.1, J2.4, R15.2
unnamed: J2.5, R10.2
unnamed: C15.1, J2.6, R16.2
unnamed: J2.7, R11.2
unnamed: J2.8, R9.2
unnamed: J2.10, R7.2
unnamed: J4.1, R17.1
unnamed: C29.1, J4.2, R27.1
unnamed: JP1.2 (B), R4.2
unnamed: MCU1.6 (PA0), R1.2
unnamed: C22.1, U3.1 (BOOT)
unnamed: R8.1, R29.1, R30.1, U3.4 (VSENSE)
unnamed: R19.2, VD1.2 (A)
unnamed: R20.2, VD2.2 (A)
ON: J3.10, R25.2
OVL: J3.3, R21.2
PA1: MCU1.7 (PA1), R21.1
PA12: MCU1.22 (PA12), R22.1
PA15: MCU1.25 (PA15), R25.1
PF0: C13.1, MCU1.2 (PF0), Y1.1
PF1: C12.1, MCU1.3 (PF1), Y1.2
PSFBV: J3.5, R5.2
PSON: J3.9, R22.2
RefI: C6.1, J3.6, R12.1
RefV: C8.1, J3.7, R23.1
RefV3: J3.1, R26.2
SCL: C9.1, J1.5, MCU1.29 (PB6), R3.1, R7.1
SDA: C10.1, J1.6, MCU1.30 (PB7), R9.1, R13.1
SPI1_MISO: MCU1.27 (PB4), R15.1
SPI1_MOSI: MCU1.28 (PB5), R14.1
SPI1_SCK: MCU1.26 (PB3), R16.1
SWCLK: J1.4, MCU1.24 (PA14)
SWDIO: J1.3, MCU1.23 (PA13)
TIM1_CH3: MCU1.20 (PA10), R31.2
VDD: C16.1, C17.1, C18.1, C27.1, C28.1, J1.2, J2.9, L1.1, MCU1.1 (Vdd), MCU1.17 (Vdd), R3.2, R4.1, R13.2, R20.1, U2.2 (VO)
VDDA: C19.1, C20.1, L1.2, MCU1.5 (AVdd), R26.1
